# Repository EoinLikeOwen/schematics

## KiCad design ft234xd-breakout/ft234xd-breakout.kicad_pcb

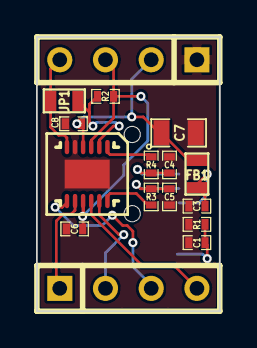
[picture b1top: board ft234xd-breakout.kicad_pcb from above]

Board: 2 copper layers, 10.2 x 15.2 mm, 17 parts (1 on the bottom side), 15 nets.

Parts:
C1: 4.7nF; SM0402_c
C3: 10nF; SM0402_c
C4, C5: 47pF; SM0402_c
C6, C8: 0.1uF; SM0402_c
C7: 4.7uF; SM0805
CON1: USB-MINI-B; USB_MINI_B
FB1: 600R/1.3A; SM0603
JP1: JUMPER; SM0603
P1, P2: CONN_4; SIL-4
R1: 1M; SM0402_r
R2: 10k; SM0402_r
R3, R4: 27R; SM0402_r
U1: FT234XD; DFN12

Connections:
3V3OUT: C6.1, P1.3, R2.2, U1.3, U1.9
CBUS0: JP1.2, P1.4, U1.6
CTS: P2.2, U1.11
D+: R3.2, U1.12
D-: R4.2, U1.1
GND: C1.2, C3.2, C4.2, C5.2, C6.2, C7.2, C8.2, CON1.5, P1.1, R1.2, U1.5, U1.13
unnamed: C5.1, CON1.2, R3.1
unnamed: C4.1, CON1.3, R4.1
unnamed: C1.1, CON1.6, R1.1
unnamed: C3.1, CON1.1, FB1.1
RESET: JP1.1, R2.1, U1.2
RTS: P2.1, U1.8
RXD: P2.4, U1.10
TXD: P2.3, U1.7
VBUS: C7.1, C8.1, FB1.2, P1.2, U1.4

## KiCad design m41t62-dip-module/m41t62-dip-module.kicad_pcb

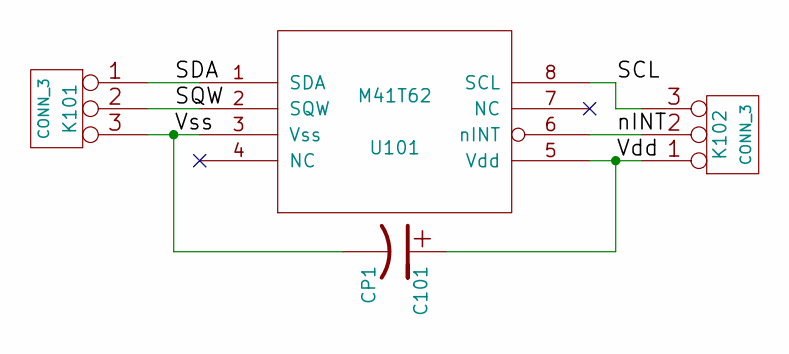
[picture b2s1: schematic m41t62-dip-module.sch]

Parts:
C101: CP1
K101, K102: CONN_3
U101: M41T62; LCC8

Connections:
/SCL: K102.3, U101.8 (SCL)
/SDA: K101.1, U101.1 (SDA)
/SQW: K101.2 (PM), U101.2 (SQW)
/Vdd: C101.1, K102.1, U101.5 (Vdd)
/Vss: C101.2, K101.3, U101.3 (Vss)
/nINT: K102.2 (PM), U101.6 (nINT)

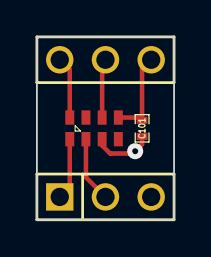
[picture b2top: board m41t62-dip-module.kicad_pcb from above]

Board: 2 copper layers, 7.6 x 10.2 mm, 4 parts (0 on the bottom side), 6 nets.

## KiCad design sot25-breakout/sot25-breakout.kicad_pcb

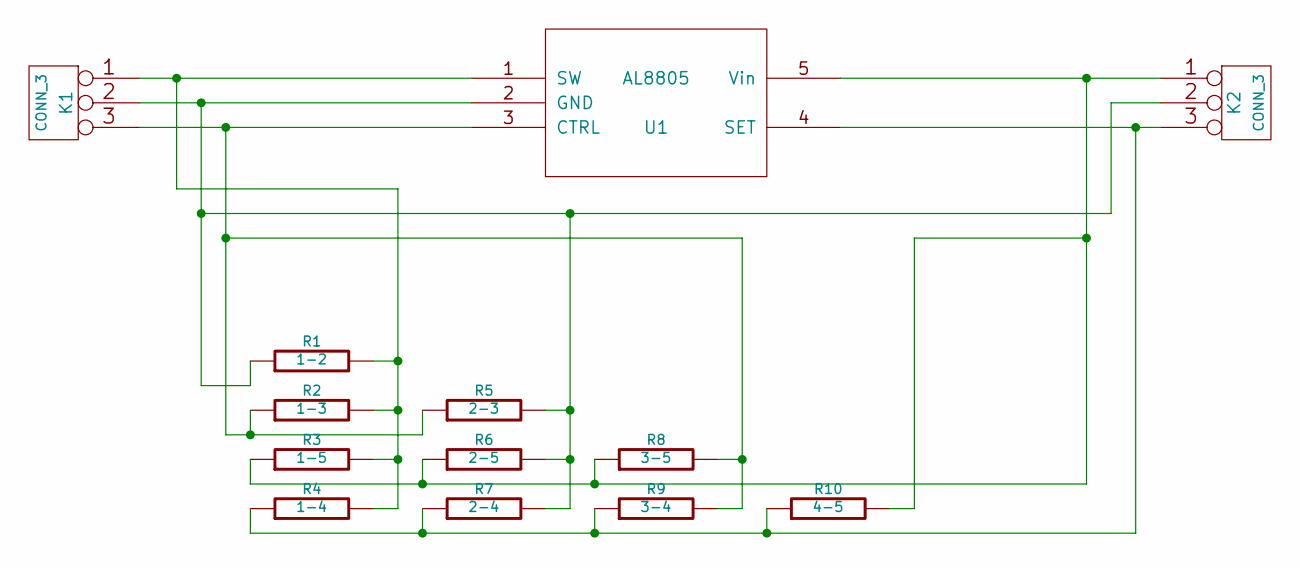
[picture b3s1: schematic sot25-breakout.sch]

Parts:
K1, K2: CONN_3
R1: 1-2
R2: 1-3
R3: 1-5
R4: 1-4
R5: 2-3
R6: 2-5
R7: 2-4
R8: 3-5
R9: 3-4
R10: 4-5
U1: AL8805; MODULE

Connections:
unnamed: K2.3, R4.1, R7.1, R9.1, R10.1, U1.4 (SET)
unnamed: K2.1, R3.1, R6.1, R8.1, R10.2, U1.5 (Vin)
unnamed: K1.3, R2.1, R5.1, R8.2, R9.2, U1.3 (CTRL)
unnamed: K1.2 (PM), K2.2 (PM), R1.1, R5.2, R6.2, R7.2, U1.2 (GND)
unnamed: K1.1, R1.2, R2.2, R3.2, R4.2, U1.1 (SW)

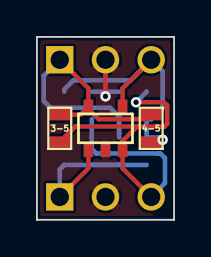
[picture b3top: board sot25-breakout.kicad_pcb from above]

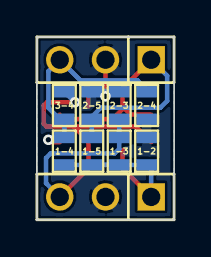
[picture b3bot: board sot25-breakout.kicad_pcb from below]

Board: 2 copper layers, 7.6 x 10.2 mm, 13 parts (10 on the bottom side), 5 nets.
